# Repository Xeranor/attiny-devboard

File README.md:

# attiny-devboard
A very simple devboard for the ATtiny25/45/85 family.

It needs to be powered from a regulated voltage source.
It breaks out:
> - 3x VCC
> - 3x GROUND
> - 1x ICSP 6PIN
> - 2x PB0-PB5

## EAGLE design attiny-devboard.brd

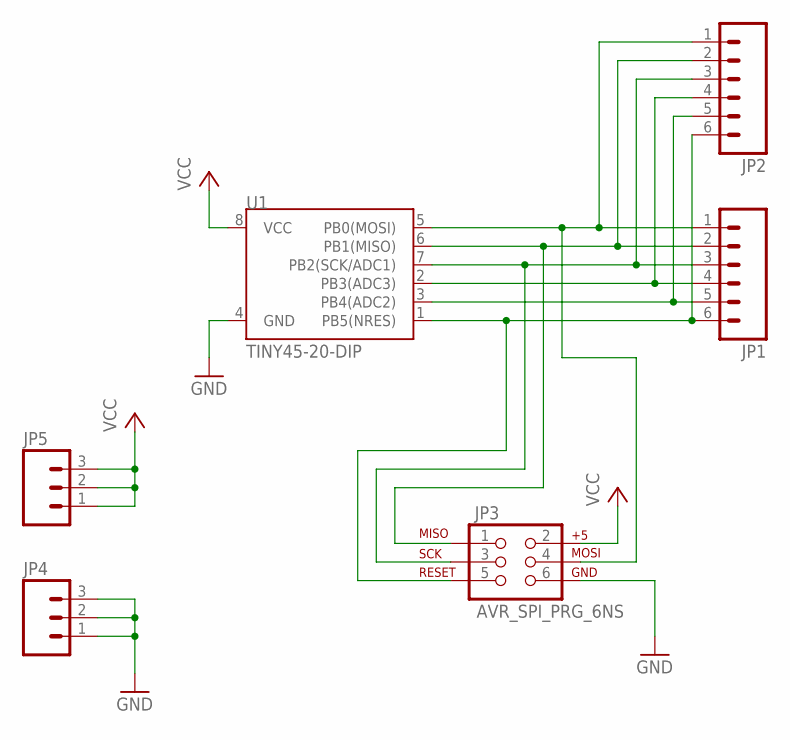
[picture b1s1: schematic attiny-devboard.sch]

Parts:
JP1, JP2: M06LOCK; 1X06_LOCK
JP3: AVR_SPI_PRG_6NS; 2X3-NS
JP4, JP5: M03LOCK; 1X03_LOCK
U1: TINY45-20-DIP; DIP08

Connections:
GND: JP3.6, JP4.1, JP4.2, JP4.3, U1.4 (GND)
unnamed: JP1.1, JP2.1, JP3.4, U1.5 (PB0(MOSI))
unnamed: JP1.2, JP2.2, JP3.1, U1.6 (PB1(MISO))
unnamed: JP1.3, JP2.3, JP3.3, U1.7 (PB2(SCK/ADC1))
unnamed: JP1.4, JP2.4, U1.2 (PB3(ADC3))
unnamed: JP1.5, JP2.5, U1.3 (PB4(ADC2))
unnamed: JP1.6, JP2.6, JP3.5, U1.1 (PB5(NRES))
VCC: JP3.2, JP5.1, JP5.2, JP5.3, U1.8 (VCC)

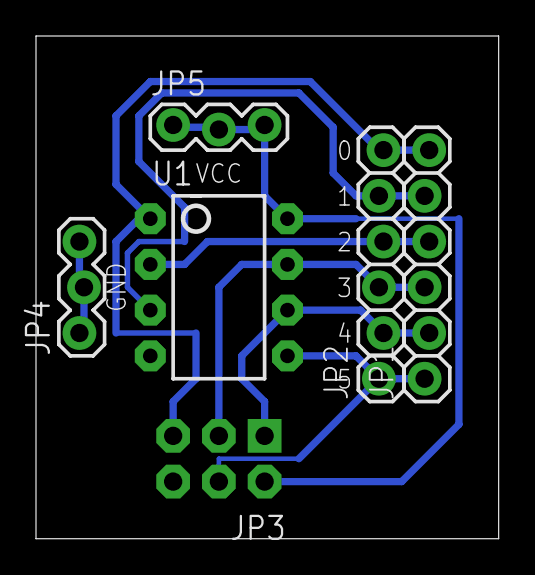
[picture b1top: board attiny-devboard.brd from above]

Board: 2 copper layers, 25.7 x 27.9 mm, 6 parts (0 on the bottom side), 8 nets.

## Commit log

2015-07-30 Initial board files
2015-07-30 Added specs to README
2015-07-30 Fixed layout

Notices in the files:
parts and their libraries:
SparkFun-Connectors: Licensing: Creative Commons ShareAlike 4.0 International - https://creativecommons.org/licenses/by-sa/4.0
